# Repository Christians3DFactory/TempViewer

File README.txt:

TEMPVIEWER
a small box box to read out all types of thermocoupels, with the abbilities to set alarms and interlocks.

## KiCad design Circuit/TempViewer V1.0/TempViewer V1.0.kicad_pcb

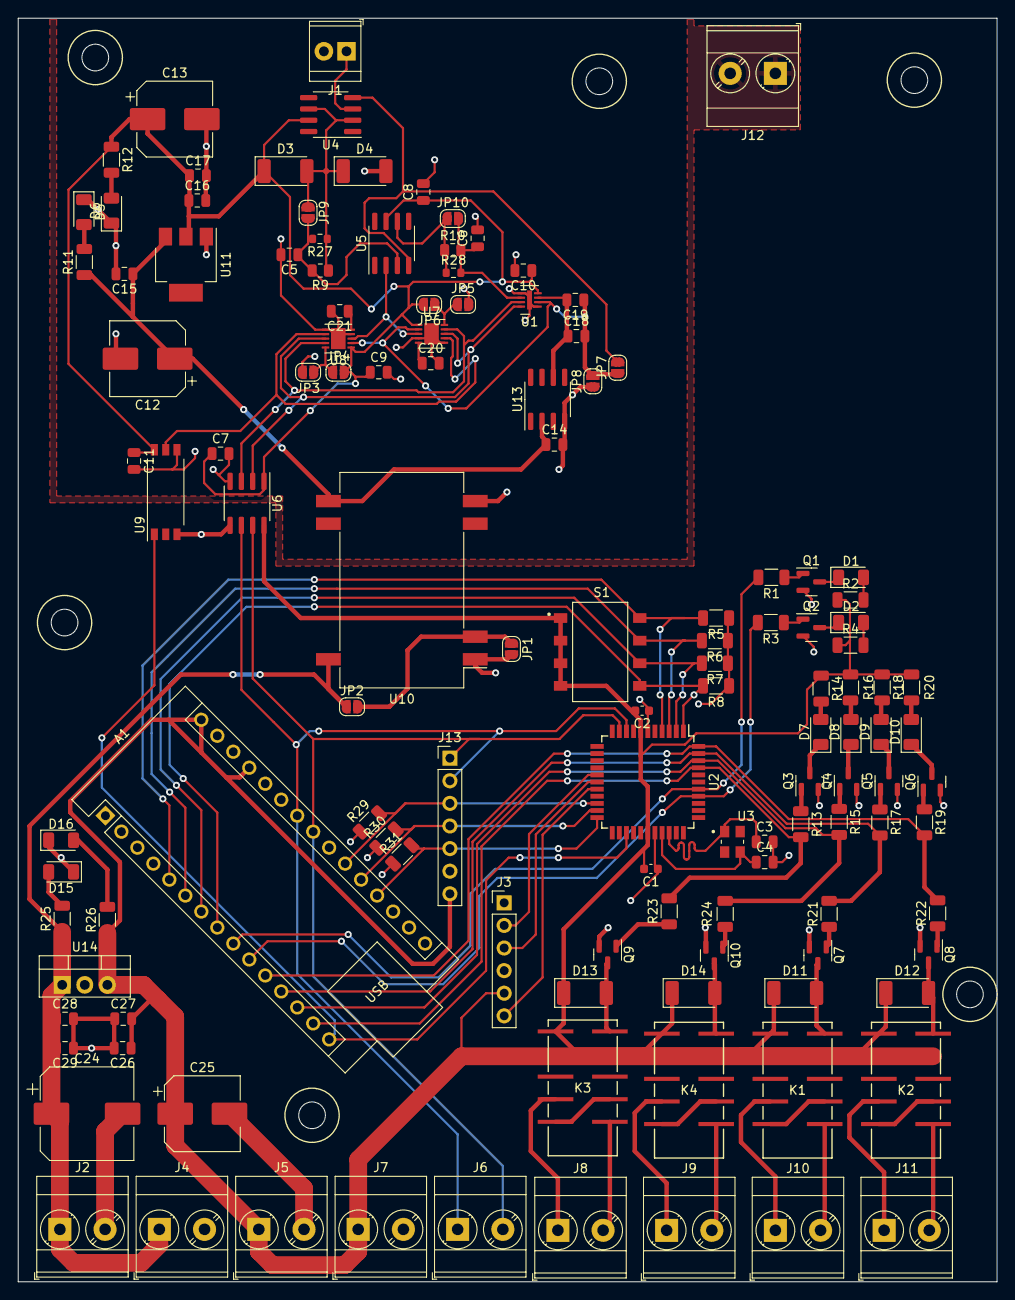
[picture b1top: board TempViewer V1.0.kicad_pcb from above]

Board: 2 copper layers, 110.0 x 142.0 mm, 126 parts (0 on the bottom side), 87 nets.

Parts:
A1: Arduino_Nano_v3.x; Arduino_Nano
C1, C2: 100nF; C_0603_1608Metric
C3, C4: 15pF; C_0805_2012Metric
C5, C6, C20, C21: C; C_0805_2012Metric
C7, C8, C9, C10, C11, C14, C15, C16, C17, C18, C26, C27, C28, C29: 100nF; C_0805_2012Metric
C12, C13, C25: 470uF; CP_Elec_8x6.7
C19: 10nF; C_0805_2012Metric
C24: 470uF; CP_Elec_10x10
D1, D2, D5, D6, D7, D8, D9, D10, D15, D16: LED; LED_1206_3216Metric
D3, D4, D11, D12, D13, D14: 1N5711UR; D_MELF
J1: Screw_Terminal_01x02; TerminalBlock_TE_282834-2_1x02_P2.54mm_Horizontal
J2: 12V IN; TerminalBlock_Phoenix_MKDS-3-2-5.08_1x02_P5.08mm_Horizontal
J3: Programming; PinHeader_1x06_P2.54mm_Vertical
J4: 12V OUT; TerminalBlock_Phoenix_MKDS-3-2-5.08_1x02_P5.08mm_Horizontal
J5: 5V IN; TerminalBlock_Phoenix_MKDS-3-2-5.08_1x02_P5.08mm_Horizontal
J6: I2C; TerminalBlock_Phoenix_MKDS-3-2-5.08_1x02_P5.08mm_Horizontal
J7: 5V OUT; TerminalBlock_Phoenix_MKDS-3-2-5.08_1x02_P5.08mm_Horizontal
J8: InterLock_1; TerminalBlock_Phoenix_MKDS-3-2-5.08_1x02_P5.08mm_Horizontal
J9: InterLock_2; TerminalBlock_Phoenix_MKDS-3-2-5.08_1x02_P5.08mm_Horizontal
J10: InterLock_3; TerminalBlock_Phoenix_MKDS-3-2-5.08_1x02_P5.08mm_Horizontal
J11: InterLock_4; TerminalBlock_Phoenix_MKDS-3-2-5.08_1x02_P5.08mm_Horizontal
J12: PE; TerminalBlock_Phoenix_MKDS-3-2-5.08_1x02_P5.08mm_Horizontal
J13: Conn_01x07_Pin; PinHeader_1x07_P2.54mm_Vertical
JP1, JP2, JP3, JP4, JP5, JP6, JP7, JP8, JP9, JP10: SolderJumper_2_Open; SolderJumper-2_P1.3mm_Open_RoundedPad1.0x1.5mm
K1, K2, K3, K4: EE2-5NU; EE2NU_KEM
Q1, Q2, Q3, Q4, Q5, Q6, Q7, Q8, Q9, Q10: DMN3731U; SOT-23
R1, R3, R13, R15, R17, R19, R21, R22, R23, R24: 1KR; R_1206_3216Metric
R2, R4, R11, R12, R14, R16, R18, R20, R26: 180R; R_1206_3216Metric
R5, R6, R7, R8, R29, R30, R31: 10KR; R_1206_3216Metric
R9, R10: R; R_0805_2012Metric
R25: R; R_1206_3216Metric
R27, R28: R; R_0603_1608Metric
S1: DS04-254-2-04BK-SMT-TR; SW_DS04-254-2-04BK-SMT-TR
U1: LTC2451xDDB; DFN-8-1EP_2x3mm_P0.5mm_EP0.56x2.15mm
U2: PIC16F18877-I/PT; TQFP-44_10x10mm_P0.8mm
U3: XTAL_ABM8-37.500MHZ-12-1-U-T
U4, U5: MAX4289ESA+ / OP37; SOIC-8_3.9x4.9mm_P1.27mm
U6: ISO1641BDR; SOIC-8_3.9x4.9mm_P1.27mm
U7, U8: AD5272BCP; LFCSP-WD-10-1EP_3x3mm_P0.5mm_EP1.64x2.38mm
U9: TLP2770; SO-6L_10x3.84mm_P1.27mm
U10: ATA00AA36S-L; Converter_DCDC_Artesyn_ATA_SMD
U11: TLV1117-33; SOT-223
U13: LTC1798CS8-3PBF; SOIC-8_3.9x4.9mm_P1.27mm
U14: LM7805_TO220; TO-220-3_Vertical

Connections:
5V: A1.27 (+5V), A1.30 (VIN), C1.2, C2.2, C25.1, C26.1, C27.2, D11.1 (K), D12.1 (K), D13.1 (K), D14.1 (K), J3.5, J5.1, J7.1, J13.7, K1.1, K2.1, K3.1, K4.1, R2.1, R4.1, R14.1, R16.1, R18.1, R20.1, R26.1, S1.1A, S1.2A, S1.3A, S1.4A, U2.7 (VDD), U2.28 (VDD), U6.8 (VCC2), U14.3 (VO)
12V: C24.1, C28.1, C29.2, J2.1, J4.1, JP2.1 (A), R25.1, U10.16 (+VIN), U14.1 (VI)
-VREF: JP7.2 (B), U4.4 (GND), U5.4 (GND)
A3V3: C7.1, C8.1, C9.1, C10.1, C11.1, C13.1, C16.1, C17.1, D3.1 (K), JP4.2 (B), JP6.2 (B), R12.1, U1.4 (VCC), U4.7 (VCC), U5.7 (VCC), U6.1 (VCC1), U7.1 (VDD), U8.1 (VDD), U9.6 (VDD), U11.2 (VO)
A5V: C12.1, C14.1, C15.1, R11.1, U10.9 (+VOUT), U11.3 (VI), U13.2 (IN)
ADDR_1: A1.5 (D2), R5.2, S1.1B, U2.4 (RD6)
ADDR_2: A1.6 (D3), R6.2, S1.2B, U2.3 (RD5)
ADDR_3: A1.7 (D4), R7.2, S1.3B, U2.2 (RD4)
ADDR_4: A1.8 (D5), R8.2, S1.4B, U2.1 (RC7)
AGND: C5.2, C6.2, C7.2, C8.2, C9.2, C10.2, C11.2, C12.2, C13.2, C14.2, C15.2, C16.2, C17.2, C20.2, C21.2, D4.2 (A), D5.1 (K), D6.1 (K), J1.2, JP3.2 (B), JP5.2 (B), JP8.1 (A), U1.1 (GND), U1.5 (GND), U1.9 (GND), U6.4 (GND1), U7.4 (VSS), U7.6 (GND), U7.11 (VSS), U8.4 (VSS), U8.6 (GND), U8.11 (VSS), U9.4 (GND), U10.8 (COM), U11.1 (GND), U13.4 (GND)
AR1.1: C18.2, C19.1, JP7.1 (A), JP8.2 (B), U1.2 (REF-), U7.2 (A), U8.2 (A)
AR1.2: U5.2 (IN-), U7.3 (W), U8.3 (W)
AR2.1: JP10.1 (A), R10.1, R28.1, U5.6 (OUT)
CycleLED: A1.9 (D6), R1.2, U2.38 (RD0)
ERRLED: A1.10 (D7), R3.2, U2.37 (RC3)
GND: A1.4 (GND), A1.29 (GND), C1.1, C2.1, C3.2, C4.2, C24.2, C25.2, C26.2, C27.1, C28.2, C29.1, D15.1 (K), D16.1 (K), J2.2, J3.4, J4.2, J5.2, J7.2, J13.6, JP1.2 (B), Q1.2 (S), Q2.2 (S), Q3.2 (S), Q4.2 (S), Q5.2 (S), Q6.2 (S), Q7.2 (S), Q8.2 (S), Q9.2 (S), Q10.2 (S), R5.1, R6.1, R7.1, R8.1, R29.1, R30.1, R31.1, U2.6 (VSS), U2.29 (VSS), U6.5 (GND2), U9.3 (K), U10.1 (-VIN), U14.2 (GND)
Interlock_1: A1.14 (D11), R13.2, R23.2, U2.41 (RD3)
Interlock_1_11: J8.1, K3.4
Interlock_1_12: J8.2, K3.8
Interlock_2: A1.13 (D10), R15.2, R24.2, U2.42 (RC4)
Interlock_2_11: J9.1, K4.4
Interlock_2_12: J9.2, K4.8
Interlock_3: A1.12 (D9), R17.2, R21.2, U2.43 (RC5)
Interlock_3_11: J10.1, K1.4
Interlock_3_12: J10.2, K1.8
Interlock_4: A1.11 (D8), R19.2, R22.2, U2.44 (RC6)
Interlock_4_11: J11.1, K2.4
Interlock_4_12: J11.2, K2.8
KnobButtom: A1.21 (A2), J13.3, R29.2, U2.20 (RA1)
Knob_1: A1.19 (A0), J13.5, R31.2, U2.22 (RA3)
Knob_2: A1.20 (A1), J13.4, R30.2, U2.21 (RA2)
unnamed: D1.2 (A), R2.2
unnamed: D1.1 (K), Q1.3 (D)
unnamed: D2.2 (A), R4.2
unnamed: D2.1 (K), Q2.3 (D)
unnamed: D3.2 (A), D4.1 (K), JP9.1 (A), R9.1, R27.1, U4.2 (IN-), U4.6 (OUT)
unnamed: D5.2 (A), R11.2
unnamed: D6.2 (A), R12.2
unnamed: D7.2 (A), R14.2
unnamed: D7.1 (K), Q3.3 (D)
unnamed: D8.2 (A), R16.2
unnamed: D8.1 (K), Q4.3 (D)
unnamed: D9.2 (A), R18.2
unnamed: D9.1 (K), Q5.3 (D)
unnamed: D10.2 (A), R20.2
unnamed: D10.1 (K), Q6.3 (D)
unnamed: D11.2 (A), K1.12, Q7.3 (D)
unnamed: D12.2 (A), K2.12, Q8.3 (D)
unnamed: D13.2 (A), K3.12, Q9.3 (D)
unnamed: D14.2 (A), K4.12, Q10.3 (D)
unnamed: D15.2 (A), R25.2
unnamed: D16.2 (A), R26.2
unnamed: J3.2, U2.16 (RB6/ICSPCLK)
unnamed: J3.3, U2.17 (RB7/ICSPDAT)
unnamed: J3.6, U2.18 (RE3/*MCLR/VPP)
unnamed: JP1.1 (A), JP2.2 (B), U10.2 (ON/~OFF)
unnamed: JP3.1 (A), JP4.1 (A), U8.10 (ADDR)
unnamed: JP5.1 (A), JP6.1 (A), U7.10 (ADDR)
unnamed: C5.1, JP9.2 (B), R9.2, R27.2, U5.3 (IN+)
unnamed: C6.1, JP10.2 (B), R10.2, R28.2, U1.6 (IN)
unnamed: K1.5, K1.9
unnamed: K2.5, K2.9
unnamed: K3.5, K3.9
unnamed: K4.5, K4.9
unnamed: Q1.1 (G), R1.1
unnamed: Q2.1 (G), R3.1
unnamed: Q3.1 (G), R13.1
unnamed: Q4.1 (G), R15.1
unnamed: Q5.1 (G), R17.1
unnamed: Q6.1 (G), R19.1
unnamed: Q7.1 (G), R21.1
unnamed: Q8.1 (G), R22.1
unnamed: Q9.1 (G), R23.1
unnamed: Q10.1 (G), R24.1
unnamed: U1.7 (SCL), U6.3 (SCL1), U7.9 (SCL), U8.9 (SCL)
unnamed: U1.8 (SDA), U6.2 (SDA1), U7.8 (SDA), U8.8 (SDA)
unnamed: C20.1, U7.5 (EXT_CAP)
unnamed: U7.7 (~RESET), U8.7 (~RESET), U9.5 (VO)
unnamed: C21.1, U8.5 (EXT_CAP)
OSC1: C4.1, U2.30 (RA7), U3.3 (2)
OSC2: C3.1, U2.31 (RA6), U3.1
PE: J12.1, J12.2
ResetR: A1.15 (D12), U2.25 (RE0), U9.1 (A)
SCL: A1.24 (A5), J6.1, J13.2, U2.9 (RB1), U6.6 (SCL2)
SDA: A1.23 (A4), J6.2, J13.1, U2.10 (RB2), U6.7 (SDA2)
Thermoelement+: J1.1, U4.3 (IN+)
VREF: C18.1, C19.2, U1.3 (REF+), U13.6 (OUT)

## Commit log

2024-02-06 Addfolders
2024-02-07 KiCad
2024-02-07 MCU Circuit
2024-02-08 Analog Circuits added
2024-05-07 PCB Design V1
2024-05-07 Mountingholes
2024-05-08 Mounting Holes
